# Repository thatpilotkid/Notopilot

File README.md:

# Notopilot
Definitely NOT a single axis altitude hold PID controlled autopilot. 

# The Scope
The scope of this project is to design, build, test, and implement a single axis, altitude preselect, autopilot for small general aviation aircraft. The budget for the project is $100 and whatever crap is sitting around my hangar. 

# The Systems
The MK1 autopilot control system consists of a 3 position momentary rocker switch, an arduino uno, a DC stepper motor driver breakout board, a battery system, and a NEMA 17 stepper motor.

# The Gameplan
The current plan for the MK1 Notopilot is to simply design, build, test, tune, and implement a simple electric trim system. The autopilot consists of a floor piece, a retention arm, a hinge, a gas spring, a NEMA 17 stepper motor, a "Nub" from AndyMark, and a 4" 35A 8mm bore compliant wheel from AndyMark. The floor piece is velcroed or zip tied to the aircrafts floor, just aft of the pedestal. At the end of the floor piece, a hinge is connected to the bottom of the retention arm, so that the angle between the floor piece is just greater than 90°, with the retention arm being the piece of the assembly closest to the pedestal. There is a gas spring, to force a positive angle between the floor piece and the retention arm, with one mounting point of the gas spring on the retention arm, the other on the floor piece. At the top of the retention arm, a NEMA 17 stepper motor is mounted with the shaft perpendicular to the aircraft centerline. Attached to the shaft of the motor, is a nub, which lets you drive AndyMark wheels using a shaft. Attached to the nub is the compliant wheel, which pushed against the trim wheel, with whatever force the gas spring is exerting on the retention arm.

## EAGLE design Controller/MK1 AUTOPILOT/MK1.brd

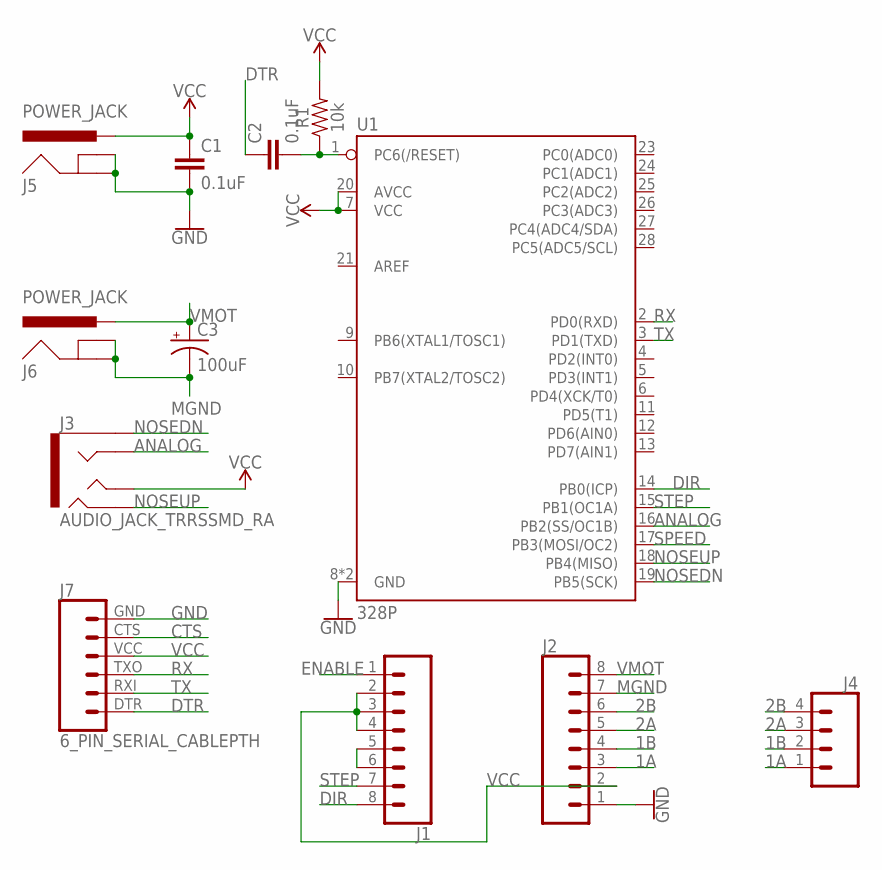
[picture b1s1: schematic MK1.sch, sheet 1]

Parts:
C1, C2: 0.1uF; CAP-PTH-SMALL-KIT
C3: 100uF; CPOL-RADIAL-2.5MM-6.5MM
J1, J2: CONN_08"; 1X08
J3: AUDIO_JACK_TRRSSMD_RA; AUDIO_JACK_3.5MM_TRRS_SMD_RA
J4: CONN_04PTH; 1X04
J5, J6: POWER_JACK; POWER_JACK_PTH
J7: 6_PIN_SERIAL_CABLEPTH; FTDI_BASIC
R1: 10k; AXIAL-0.3
U1: 328P; DIP28

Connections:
1A: J2.3, J4.1
1B: J2.4, J4.2
2A: J2.5, J4.3
2B: J2.6, J4.4
ANALOG: J3.RING1, U1.16 (PB2(SS/OC1B))
CTS: J7.CTS (5)
DIR: J1.8, U1.14 (PB0(ICP))
DTR: C2.1, J7.DTR (1)
ENABLE: J1.1
GND: C1.2, J2.1, J5.GND, J5.GNDBREAK, J7.GND (6), U1.8 (GND), U1.22 (GND)
MGND: C3.2 (-), J2.7, J6.GND, J6.GNDBREAK
unnamed: C2.2, R1.P$1 (1), U1.1 (PC6(/RESET))
unnamed: J1.5, J1.6
NOSEDN: J3.EARTH, U1.19 (PB5(SCK))
NOSEUP: J3.RING2, U1.18 (PB4(MISO))
RX: J7.TXO (3), U1.2 (PD0(RXD))
SPEED: U1.17 (PB3(MOSI/OC2))
STEP: J1.7, U1.15 (PB1(OC1A))
TX: J7.RXI (2), U1.3 (PD1(TXD))
VCC: C1.1, J1.2, J1.3, J1.4, J2.2, J3.TIP, J5.PWR, J7.VCC (4), R1.P$2 (2), U1.7 (VCC), U1.20 (AVCC)
VMOT: C3.1 (+), J2.8, J6.PWR

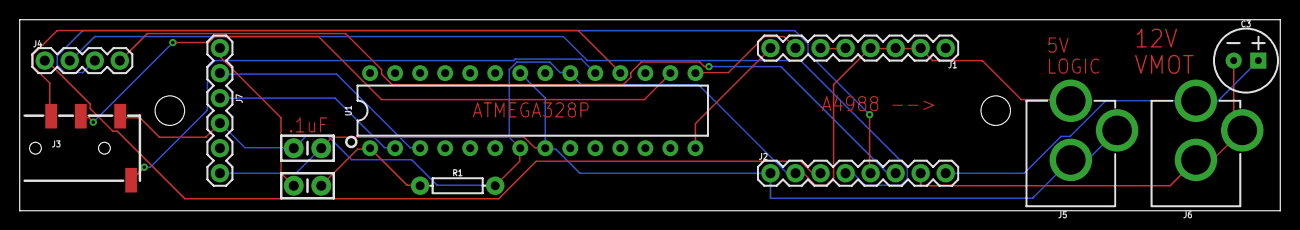
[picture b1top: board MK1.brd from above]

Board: 2 copper layers, 127.9 x 19.4 mm, 12 parts (0 on the bottom side), 18 nets.

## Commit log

2020-12-16 Design README.md
2020-12-16 Added MK1 System Image
2020-12-16 Testing Adding Images
2020-12-16 Added system image
2021-01-13 Added academic research paper
    https://www.researchgate.net/publication/292993131_Improvements_of_a_flying-wing_Micro-Air-Vehicle_by_closing_the_control-loop_on_ground
2021-01-13 Added Stepper Motor Mount 2020E.SLDPRT
    NEMA 17 stepper motor gets mounted onto this sheet metal part, and that gets mounted to a 2020 extrusion.
2021-01-13 Added a bunch of crap
    Added miscellaneous files to be edited/organized later.
2021-01-13 Copied Main Assembly to main
2021-01-14 Did some stuff that I forgot to document
    I edited some parts and assemblies
2021-01-20 Added simple stepper tester file
    WHY THE FUCK IS THIS SO DIFFICULT
2021-01-25 Added MK1 PCB from EAGLE

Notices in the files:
parts and their libraries:
SparkFun-Capacitors: Licensing: Creative Commons ShareAlike 4.0 International - https://creativecommons.org/licenses/by-sa/4.0
